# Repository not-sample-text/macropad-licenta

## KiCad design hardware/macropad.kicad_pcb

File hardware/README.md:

# Hardware

Conține toate fișierele de proiectare în KiCad, precum și fișierele de ieșire pentru fabricație.

Conținut:

- `macropad.kicad_pro` – Fișierul principal al proiectului KiCad
- `macropad.kicad_sch` – Schemă electrică: Pico, switch-uri, encoder, OLED, diode
- `macropad.kicad_pcb` – Layout-ul PCB-ului
- `outputs/` – Gerber, BOM și fișiere pick-and-place pentru fabricație
- `custom_parts/` – Simboluri, amprente sau modele 3D personalizate

Folosește acest director pentru modificări în proiectarea electrică sau pentru generarea fișierelor de producție.

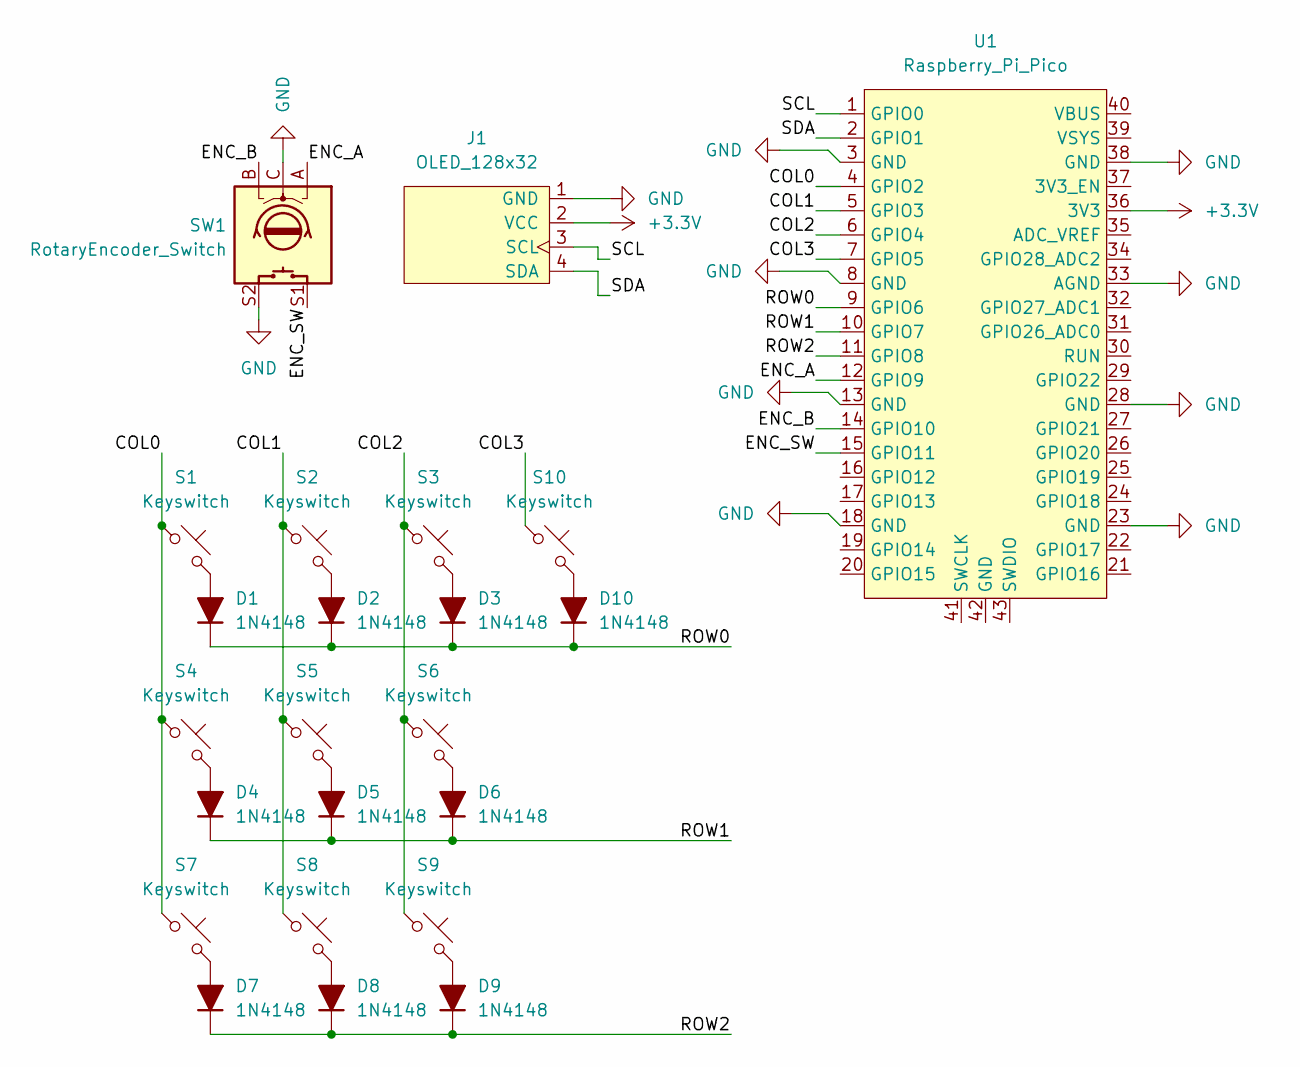
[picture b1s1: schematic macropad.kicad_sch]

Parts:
D1, D2, D3, D4, D5, D6, D7, D8, D9, D10: 1N4148; D_DO-35_SOD27_P7.62mm_Horizontal
J1: OLED_128x32
S1, S2, S3, S4, S5, S6, S7, S8, S9, S10: Keyswitch; Hotswap_MX_1.00u
SW1: RotaryEncoder_Switch; Encoder_EC11_MX
U1: Raspberry_Pi_Pico

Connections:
+3.3V: J1.2 (VCC), U1.36 (3V3)
/COL0: S1.1, S4.1, S7.1, U1.4 (GPIO2)
/COL1: S2.1, S5.1, S8.1, U1.5 (GPIO3)
/COL2: S3.1, S6.1, S9.1, U1.6 (GPIO4)
/COL3: S10.1, U1.7 (GPIO5)
/ENC_A: SW1.A, U1.12 (GPIO9)
/ENC_B: SW1.B, U1.14 (GPIO10)
/ENC_SW: SW1.S1, U1.15 (GPIO11)
/ROW0: D1.1 (K), D2.1 (K), D3.1 (K), D10.1 (K), U1.9 (GPIO6)
/ROW1: D4.1 (K), D5.1 (K), D6.1 (K), U1.10 (GPIO7)
/ROW2: D7.1 (K), D8.1 (K), D9.1 (K), U1.11 (GPIO8)
/SCL: J1.3 (SCL), U1.1 (GPIO0)
/SDA: J1.4 (SDA), U1.2 (GPIO1)
GND: J1.1 (GND), SW1.C, SW1.S2, U1.3 (GND), U1.8 (GND), U1.13 (GND), U1.18 (GND), U1.23 (GND), U1.28 (GND), U1.33 (AGND), U1.38 (GND)
unnamed: D1.2 (A), S1.2
unnamed: D2.2 (A), S2.2
unnamed: D3.2 (A), S3.2
unnamed: D4.2 (A), S4.2
unnamed: D5.2 (A), S5.2
unnamed: D6.2 (A), S6.2
unnamed: D7.2 (A), S7.2
unnamed: D8.2 (A), S8.2
unnamed: D9.2 (A), S9.2
unnamed: D10.2 (A), S10.2

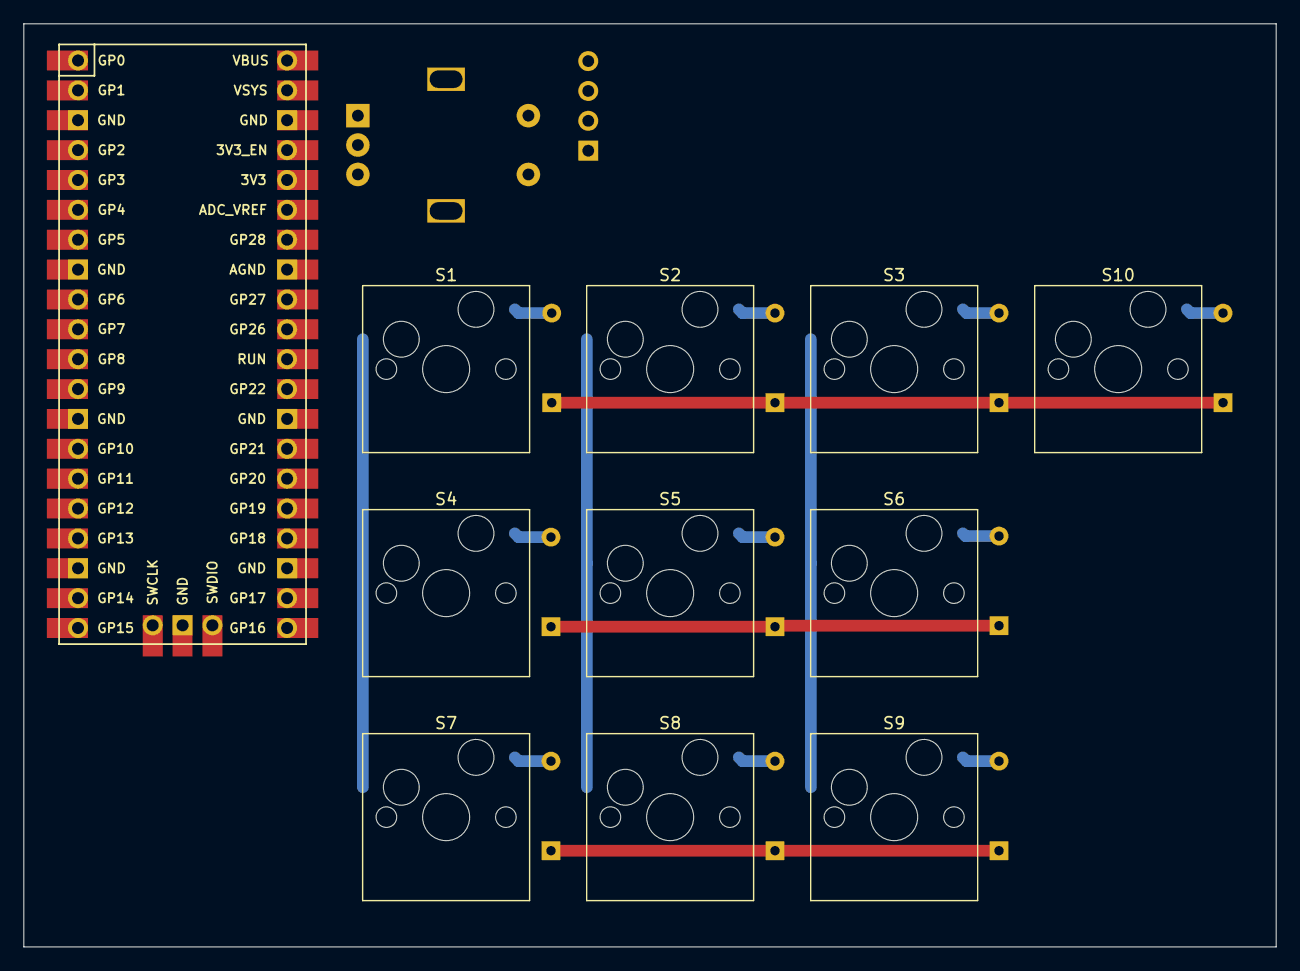
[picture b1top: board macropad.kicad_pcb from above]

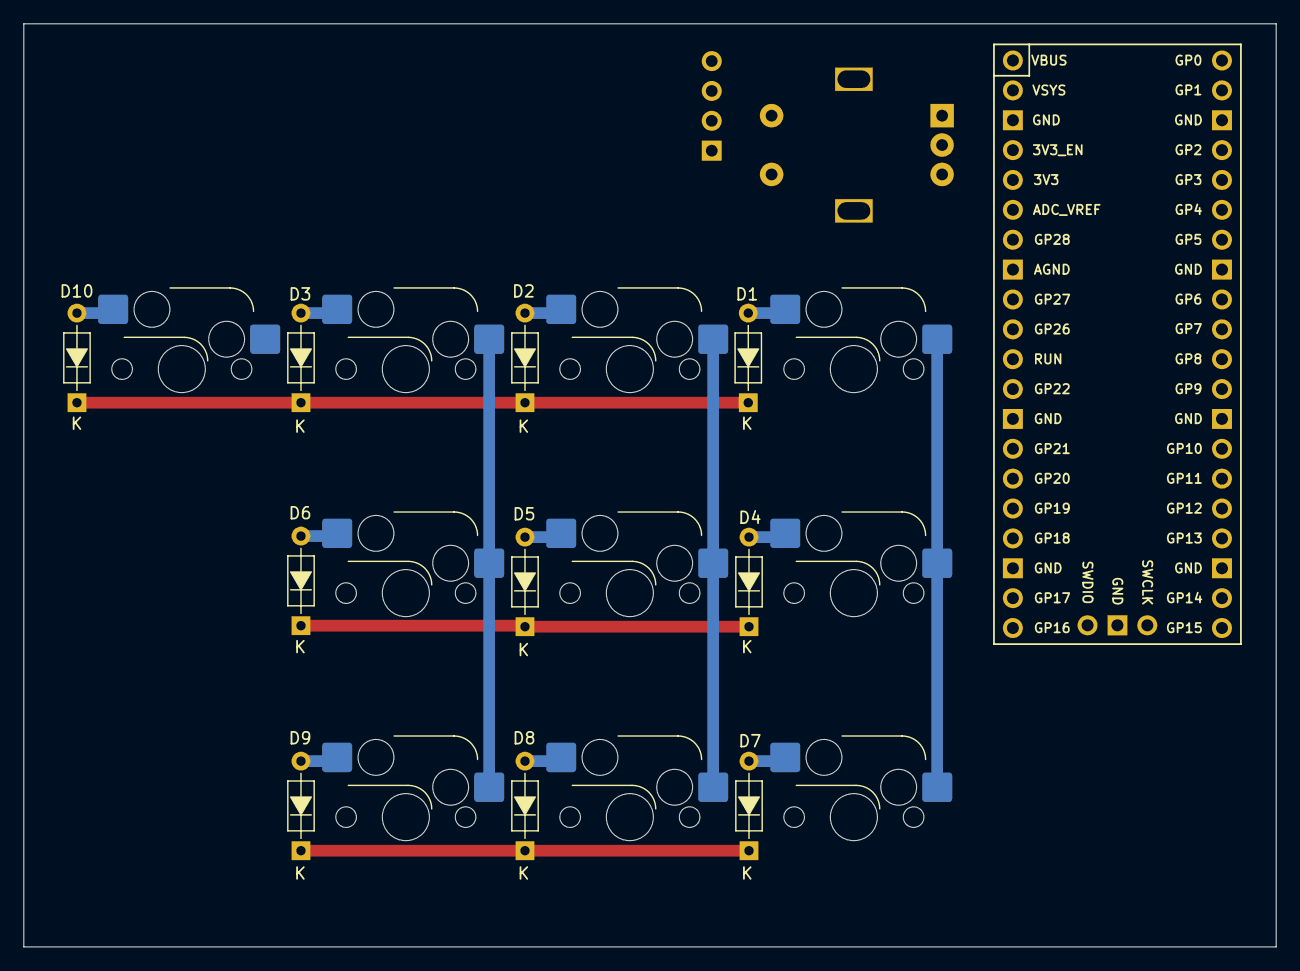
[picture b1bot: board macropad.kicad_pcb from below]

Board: 2 copper layers, 106.5 x 78.5 mm, 23 parts (10 on the bottom side), 24 nets.

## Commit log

2025-05-04 Add initial project structure and documentation
2025-05-07 updated schematic, removed everything from pcbnew
